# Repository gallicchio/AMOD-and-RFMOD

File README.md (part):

# AMOD and RF-MOD: boards of analog and RF building blocks

Nine 100 x 100 mm boards of "tiles" for an FPGA with fast converters: seven first-level boards (for the ECP5-2ADC-2DAC
board, or an Icepi Zero with its AD9280/AD9708 module), among them AMOD-N, as simple as the first, the conversion board
AMOD-C and two motor boards, AMOD-M (brushed motors and actuators) and AMOD-B (a brushless gimbal motor), and two
second-level boards built around the ECP5-2ADC-2DAC board's two DACs and two ADCs: PhMOD (AMOD-2 until Prompt 17) and
IQ-MOD.  Each tile is one circuit with its own SMA jacks: cable a DAC to its input and its
output to an ADC, and compare the measurement with the expected result printed beside it.  The silkscreen draws every
tile's wiring as it is laid in copper.  The tutorial they serve is `icepi-zero-dac-adc/tutorial/`, whose Appendix D
specified them.

Rev A, 2026-10-25 (AMOD-N, AMOD-C, AMOD-M and AMOD-B added 2026-10-28).  Designed by Claude with Jason Gallicchio.  Ordered
from JLCPCB from 2026-10-29; some of the boards have come in, all untested as of 2026-11-16 (which ones, and how many are
assembled, goes into `BRINGUP.md` when Jason says).  The bring-up is [`BRINGUP.md`](BRINGUP.md); what rev B changes is
[`bringup/REVB.md`](bringup/REVB.md), which since 2026-11-16 includes a pin audit's findings on the built boards.

**The rev A Pmod plugs are not standard** (Jason, 2026-11-16).  They were drawn to mate with ECP5-2ADC-2DAC rev A's
sockets, and both are mirrored end to end against the Pmod specification: a rev A board belongs only in an ECP5-2ADC-2DAC
rev A, never in a standard Pmod host, module or cable, where its 3.3 V and ground meet I/O lines.  The rev A boards are
marked so.  Rev B's plugs will follow the specification, as the redrawn Icepi adapter's socket now does.

| board | what | tiles | layers | parts per board |
|---|---|---|---|---|
| [AMOD-P](docs/HANDBOOK_amod_p.md) | passive: pads, RC and LC filters, resonators, a crystal, a clipper, a delay line, LEDs, an AM loopstick | 13 | 2 | $17.07 |
| [AMOD-N](docs/HANDBOOK_amod_n.md) | the second passive board: calibration standards, two splitters, a quarter-wave stub, a low-pass, a diode detector, a bias-T, a 1:1 balun and a 1:4 transformer; a step attenuator (by hand or the FPGA) and an oscillator on the Pmod's 3.3 V | 11 | 4 | $43.91 |
| [AMOD-A](docs/HANDBOOK_amod_a.md) | active on USB-C: gain blocks, an HF LNA, an HB100 Doppler radar, a one-pin ADC, a 4046 PLL, heat, a mixer, impedance and I-V, ultrasound, audio | 12 | 4 | $49.73 |
| [AMOD-C](docs/HANDBOOK_amod_c.md) | conversion: two regulators and an electronic load, a charge pump, switched capacitors (a filter, a resistor), a delta-sigma modulator, a track-and-hold, a SAR comparator, a differential pair, a cascode, a V-to-F, a precision rectifier | 12 | 4 | $43.93 |
| [AMOD-M](docs/HANDBOOK_amod_m.md) | motors on a 5-16 V supply: a DC motor with its encoder, a stepper, a servo, a solenoid's flyback three ways, a DC-coupled bridge amplifier, a buck power stage, and a hall, an optical and a load-cell sensor for their loops | 11 | 4 | $36.49 |
| [AMOD-B](docs/HANDBOOK_amod_b.md) | a brushless gimbal motor on a 5-12 V supply: a three-phase driver from the FPGA, the motor over a magnetic encoder, two halls and an index sensor, its back-EMF, its phase and bus currents, its vibration, and an IMU | 12 | 4 | $42.45 |
| [RF-MOD](docs/HANDBOOK_rf_mod.md) | 915 MHz and 2.4 GHz: a diode-ring mixer, two filters, a QPL9547 LNA, a gain block, two ADL5350 mixers, a synthesizer with two outputs, a TRF3722 I/Q transmitter, power and a 25 MHz reference | 10 | 4 | $66.51 |
| [PhMOD](docs/HANDBOOK_phmod.md) | physics at HF, magnetic resonance, the ionosphere and light: a 1 W pulse amplifier and duplexer, a two-channel HF receiver, a VLF loop amplifier, a reflection bridge, coupled resonators, a coil driver, a noise source, a laser driver with an RF bias-T | 10 | 4 | $77.89 |
| [IQ-MOD](docs/HANDBOOK_iq_mod.md) | coherent I/Q and microwave physics, 0.4-6 GHz: an I/Q modulator and demodulator on one synthesizer's two outputs, a dual directional coupler, an LNA, a log detector, a switch, a noise source, GNSS, an ODMR loop | 11 | 4 | $99.71 |
| [Icepi adapter](icepi_adapter/README.md) | the tutorial's 2x12 Icepi Zero adapter with a Pmod socket, redrawn to the Pmod standard on 2026-11-16 (never built; a rev A AMOD plug fits it only upside down) | | 4 | hand-soldered |

Each tile's name and what it does are printed on the board: the jacks' names sit on their own tile's frame beside each
jack, a tile's title in words on its top frame where it fits, its ranges and levels inside it.  Ports are named in
capitals (IN, OUT, LO), tiles in mixed case (Step attenuator, Diode mixer), everything else in lower case.  Turn a board
over and each tile has a panel on the back under it: its limits, its loads, its supply, and where there is room a small
plot of the response to expect, so the board can be cabled without the handbook open.  Below, each board's
picture and a table of its tiles, each row a summary of the tile's entry in the board's handbook (linked from the tile's
number), where the tile has its own picture, what to expect, the circuit and its parts.  What to buy beside the boards,
with links and prices, is in [docs/KIT.md](docs/KIT.md).

## The boards

<!-- board:amod_p -->
### [AMOD-P](docs/HANDBOOK_amod_p.md): the passive board

| tile | what it does | chip | specs | limits | experiments | how to use it | you need |
|---|---|---|---|---|---|---|---|
| [**p1**](docs/HANDBOOK_amod_p.md#p1) pi pad | Divides the voltage by 10 (-20 dB) and looks like 50 ohm from both ports. | passive | 61.9 / 249 / 61.9 ohm pi; -20.0 dB; DC to well past 30 MHz. | -20 dB only between 50 ohm on both sides (-14 dB into a high impedance); about 0.1 W (+-3 V) at IN. | A known weak signal for a receiver or LNA; padding a mismatched cable; checking the ADC's 50 ohm setting. | DAC to IN, OUT to the ADC set to 50 ohm. | Nothing beyond SMA cables. |
| [**p2**](docs/HANDBOOK_amod_p.md#p2) RC low-pass | A first-order RC low-pass: passes below 159 kHz and falls 20 dB per decade above. | passive | 1 k and 1 nF; -3 dB at 159 kHz; time constant 1 us. | OUT is a 1 k source: read it on the ADC's high-impedance setting (50 ohm divides it by 21). | A Bode plot, 45 degrees at the corner, the step response, the lag plant for feedback control. | DAC to IN, OUT to the ADC on high impedance; sweep the frequency or send a step. | Nothing beyond SMA cables. |
| [**p3**](docs/HANDBOOK_amod_p.md#p3) RC high-pass | A first-order RC high-pass, the mirror image of p2. | passive | 1 nF and 1 k; -3 dB at 159 kHz; +20 dB per decade below. | OUT is a 1 k source: read it on high impedance. | A Bode plot, AC coupling, a differentiator (a step gives a 1 us spike). | DAC to IN, OUT to the ADC on high impedance. | Nothing beyond SMA cables. |
| [**p4**](docs/HANDBOOK_amod_p.md#p4) series RLC | A series 100 uH and 220 pF resonator between 50 ohm ports: a band-pass peak that the DIP switch moves. | passive | 1.07 MHz with both switches off, 0.98 (way 1, +47 pF), 0.89 (way 2, +100 pF), 0.83 (both); Q about 6. | The 50 ohm ports load it: Q is 6, where the coil alone would allow about 60. | Resonance and Q, the phase through resonance, tracking a resonance with a lock-in or a PLL, a resonant plant to control. | Sweep the DAC into IN, OUT to the ADC (50 ohm); set the DIP switch. | Nothing beyond SMA cables. |
| [**p5**](docs/HANDBOOK_amod_p.md#p5) LC low-pass | A 5th-order Butterworth LC low-pass at 9 MHz: the anti-alias filter for a 25 MS/s ADC, or the smoothing filter after a DAC. | passive | -3 dB at 8.9 MHz, -30 dB at 18 MHz; 50 ohm in and out. | The response is as designed only with 50 ohm on both ports. | Aliasing with and without it; a filter's magnitude, phase and group delay; cleaning a DAC's staircase. | Between the DAC and its load, or between a signal and the ADC (50 ohm). | Nothing beyond SMA cables. |
| [**p6**](docs/HANDBOOK_amod_p.md#p6) LC low-pass | A 3rd-order LC low-pass near 120 kHz: turns a one-bit (delta-sigma or PWM) stream into a tone. | passive | 10 nF, 150 uH, 10 nF (C0G); -3 dB at 118 kHz; 50 ohm. | Designed for 50 ohm on both ports. | One-bit DAC reconstruction, delta-sigma noise shaping seen at the output, a slow plant for control. | DAC (or a one-bit stream through 50 ohm) to IN, OUT to the ADC. | Nothing beyond SMA cables. |
| [**p7**](docs/HANDBOOK_amod_p.md#p7) band-pass | A 3rd-order LC band-pass, 4.7-7.5 MHz: the band round the tutorial's 6.25 MHz digital-communications carrier. | passive | Peak at 6.3 MHz, -3 dB from 4.7 to 7.5 MHz; 50 ohm. | Only 3rd order: the skirts fall about 18 dB per octave. | Band-limiting a modem's chips (spread spectrum, LoRa chirps); a transmitter's harmonics removed; a receiver's front end. | In line between the DAC and the ADC, or ahead of a receiver. | Nothing beyond SMA cables. |
| [**p8**](docs/HANDBOOK_amod_p.md#p8) quartz crystal | A 4 MHz quartz crystal in series between the jacks: a very sharp pass at its series resonance and a notch at its parallel resonance about 6 kHz above. | passive | f_s near 4.000 MHz (-3.7 dB); f_p about 6 kHz higher; Q about 50,000 (C_m 15 fF, C_0 4 pF). | Needs frequency steps of a few hertz (the FPGA's NCO); keep the drive under about +-1 V (crystals have a drive-level limit near 100 uW). | Q from the width and from the ring-down; series against parallel resonance; pulling f_p with a capacitor across OUT (an SMA tee); the temperature coefficient. | Sweep the DAC slowly through 4.000 MHz into IN, OUT to the ADC, lock-in detection in the gateware. | An SMA tee and a few capacitors (or open cable stubs) for the pulling experiment. |
| [**p9**](docs/HANDBOOK_amod_p.md#p9) ceramic res. | A 455 kHz ceramic resonator in series: a pass at 455 kHz and a notch a few kHz above; the AM superhet's IF element. | passive | Q of a few hundred: between p4's LC (6) and p8's quartz (50,000). | A two-terminal resonator, not a three-terminal IF filter: one peak, no flat passband. | Q compared across LC, ceramic and quartz; an IF stage for a superhet built in gateware. | Sweep 440-480 kHz into IN, OUT to the ADC. | Nothing beyond SMA cables. |
| [**p10**](docs/HANDBOOK_amod_p.md#p10) clipper | 1 k in series and a 1N4148 diode each way to ground: clips any signal to about +-0.6 V. | passive | Clips at +-0.6 V; a 1 k source. | Read OUT on high impedance; up to +-4 V in (the 1 k holds the diode current to 4 mA). | Harmonics of a clipped sine against amplitude; odd harmonics, and even ones with a DC offset added; distortion. | DAC sine to IN, OUT to the ADC on high impedance, FFT in the gateware or Python. | Nothing beyond SMA cables. |
| [**p11**](docs/HANDBOOK_amod_p.md#p11) delay line | A 400 ns, 50 ohm delay line made of 20 LC sections, with taps every 100 ns: 260 feet of RG-58 on a board. | passive | Z0 51 ohm, 20 ns a section, cut-off 16 MHz, flat to about 10 MHz; taps through 470 ohm. | Disperses near 16 MHz (a chirp spreads); a tap is x1 into a high impedance, /10 into 50 ohm. | Reflections from an open, a short and a matched end; time-domain reflectometry; echoes for an equalizer; a radar target on a cable; a pure-delay plant for control. | A pulse or chirp from the DAC into IN; OUT open, shorted or terminated; the taps and OUT to the ADCs. | An SMA short and a 50 ohm terminator (the kit's ANNE-50+) for the reflection experiments. |
| [**p12**](docs/HANDBOOK_amod_p.md#p12) LEDs | Four LEDs (red, yellow, green, blue) behind 100 ohm, one at a time from the DIP switch: Planck's constant from the voltage where each starts to glow. | passive | 630, 596, 525 and 469 nm (DIP ways 1-4); 100 ohm in series; IN 0-5 V. | The InGaN green and blue sit above the line (their knee is not just hc / e lambda); the colours are not printed, so light them. | Planck's constant; LED I-V curves (with AMOD-A's a10); light against current. | Ramp the DAC (or the host's LED output) into IN and read the LED loop's voltage; one DIP way at a time. | Nothing (a dark room helps). |
| [**p13**](docs/HANDBOOK_amod_p.md#p13) AM loopstick | An AM-band antenna: a ferrite-rod coil screwed into the terminal, tuned by four switched capacitors or an external tuning capacitor on VAR C, its tap on the jack. | passive | With a 330 uH coil: 1.28 MHz (47 pF) down to 0.40 MHz (470 pF), and the sums between; the kit's 240 uH coil tunes about 17 % higher. | The switches tune in 15 steps; continuous tuning needs a capacitor on VAR C (a polyvaricon and its dial are 20 mm square: no room on the tile).  A weak signal that needs a4's gain before the ADC. | Real AM stations; the resonance and Q of a loopstick; the tutorial's AM radio gateware. | Coil ends to GND and HOT, its tap (if it has one) to TAP; rod along the bottom edge with two cable ties; OUT to AMOD-A's a4, a4 to the ADC; the DIP picks the band, or a tuning capacitor on VAR C (frame to GND) tunes within it. | An AM loopstick coil and two cable ties (kit: Atomic-29 240 uH loopstick, Panduit PLT1M-C); optionally a 365 pF tuning capacitor with a knob (kit: Amplified Parts single-section 365 pF). |

More on each tile, with its picture, in the [AMOD-P handbook](docs/HANDBOOK_amod_p.md); what to buy in [KIT.md](docs/KIT.md).

<!-- /board:amod_p -->

<!-- board:amod_n -->
### [AMOD-N](docs/HANDBOOK_amod_n.md): the second passive board

| tile | what it does | chip | specs | limits | experiments | how to use it | you need |
|---|---|---|---|---|---|---|---|
| [**n1**](docs/HANDBOOK_amod_n.md#n1) calibration | Calibration standards for a network analyzer, on the board: a short and an open at the jacks' pins, a 50 ohm load, a 25 ohm check standard and a thru. | passive | SHORT: the centre pin poured to ground all round.  OPEN: the bare pin.  LOAD: 2 x 100 ohm at the end of 4 mm of 50 ohm line.  25 OHM: 2 x 49.9 ohm (VSWR 2, \|Gamma\| 1/3, 9.5 dB return loss).  THRU: 19.8 mm of 50 ohm coplanar line, about 115 ps. | The standards are modelled, not measured: the open's fringing (tens of fF) and the short's inductance (tens of pH) count above about 3 GHz, and the 0402 load is a 20 dB return loss at 3 GHz.  Check them once against the NanoVNA's SMA standards. | A full SOLT calibration of IQ-MOD's reflectometer (q1, q2, q5) or of a NanoVNA at the board's surface; the 25 ohm standard as its check; every other tile then measured from its pads with its jacks taken out (they are all the same part). | The analyzer's port to SHORT, OPEN and LOAD in turn; its two ports to THRU A and THRU B for the two-port step; then any tile. | Nothing beyond SMA cables. |
| [**n2**](docs/HANDBOOK_amod_n.md#n2) resistive splitter | A resistive power splitter: three 16.9 ohm in a star, every port 50 ohm, 6 dB from any port to either other, from DC to 6 GHz. | passive | 3 x 16.9 ohm (50 / 3); -6.0 dB each way; DC-6 GHz; OUT 1 and OUT 2 on lines of equal length. | No isolation (OUT 1 to OUT 2 is also -6 dB); 6 dB of loss where a transformer splitter loses 3; about +20 dBm at IN (1/16 W resistors). | One DAC into both ADCs to measure the converters' own gain and skew; the reference and test paths of a scalar network analyzer; its isolation against n3's. | IN from the source; OUT 1 and OUT 2 to two 50 ohm loads.  Symmetric: any port can be IN. | Nothing beyond SMA cables. |
| [**n3**](docs/HANDBOOK_amod_n.md#n3) transformer splitter | A transformer power splitter (and combiner): half the power to each port, 3 dB, with the two ports isolated from each other, 0.5-400 MHz. | [ADP-2-1+](https://www.minicircuits.com/WebStore/dashboard.html?model=ADP-2-1%2B) | 3.1-3.4 dB from SUM to each port; 25-34 dB between port 1 and port 2; 0.5-400 MHz (the datasheet). | A transformer: nothing below 0.5 MHz; the isolation holds only with 50 ohm on all three ports; pins 2 and 5 are joined and must not be grounded. | Two DACs combined into one amplifier for a two-tone intermodulation test (AMOD-A's a4, PhMOD's h5); one reference split to two boards; isolation measured against n2's. | SUM from the source (or to the load when combining); PORT 1 and PORT 2 to two loads (or from two sources). | Nothing beyond SMA cables. |
| [**n4**](docs/HANDBOOK_amod_n.md#n4) quarter-wave stub | A quarter-wave open stub hanging off a 50 ohm line: at 2.45 GHz it is a short circuit at the junction, so the line has a notch there. | passive | 17.3 mm of 50 ohm coplanar waveguide, open at its end; a notch near 2.45 GHz and 7.35 GHz; the line passes at DC and 4.9 GHz. | The notch sits where the line's effective permittivity puts it (3.1 was assumed): within a few percent of 2.45 GHz.  Its depth is set by the line's loss. | Sweep it with RF-MOD's synthesizer into IQ-MOD's log detector, or with a VNA; read the line's effective permittivity from the notch; a Wi-Fi notch ahead of a receiver; the tutorial's coaxial quarter-wave stub at microwave frequencies. | IN from a source, OUT to a detector or a VNA's second port. | Nothing beyond SMA cables. |
| [**n5**](docs/HANDBOOK_amod_n.md#n5) low-pass | A low-pass filter: passes DC to 1 GHz, stops 1.9-5 GHz, so a 915 MHz synthesizer's harmonics are gone. | [LFCN-1000+](https://www.minicircuits.com/WebStore/dashboard.html?model=LFCN-1000%2B) | 0.3 dB at 500 MHz, 0.8 dB at 1 GHz, 3 dB at 1.3 GHz, 26 dB at 1.5 GHz, 30 dB from 1.9 to 5 GHz (the datasheet). | 50 ohm on both sides; the stopband rises again above about 5 GHz (20 dB at 5.5 GHz). | A MAX2871's square-ish 915 MHz made a sine (its harmonics before and after on a spectrum analyzer); an image filter ahead of a receiver below 1 GHz. | IN from the source, OUT to the load. | Nothing beyond SMA cables. |
| [**n6**](docs/HANDBOOK_amod_n.md#n6) detector | A diode detector: RF power in, DC out.  Two zero-bias Schottky diodes as a voltage doubler, square-law at low power and linear at high. | [SMS7630](https://www.skyworksinc.com/Products/Diodes/SMS7630-Series) | 51 ohm across IN; 10 nF in; a SMS7630 pair as a doubler; 100 pF and 100 k on OUT (about 1 us); 10 MHz-6 GHz; square law below about -20 dBm. | OUT must go to a high impedance (the ADC's high-Z setting): 50 ohm shorts it.  Microvolts at the bottom (the x100 input below -40 dBm); temperature moves its zero; +10 dBm at most (the diodes' 1 V breakdown). | Square law against the AD8318's log law (IQ-MOD); an AM envelope detector after AMOD-P's loopstick and AMOD-A's LNA; a radiometer's power detector; the shape of PhMOD's transmit pulses. | IN from the RF; OUT to an ADC on its high-impedance setting. | Nothing beyond SMA cables. |
| [**n7**](docs/HANDBOOK_amod_n.md#n7) bias-T | A bias-T: puts DC from a bench supply onto an RF line and keeps it off the RF side. | passive | 100 nF in series; 27 nH + 330 nH + 10 uH from the DC loop to RF+DC; 100 nF across the DC; about 2 MHz-3 GHz; up to 100 mA and 16 V. | Below about 2 MHz the 10 uH stops blocking; 100 mA (the 330 nH) and 16 V (the capacitors); never put RF+DC into a jack that cannot take the DC. | An active GPS antenna or an LNA at the end of a cable powered through the coax; a varactor or a detector diode biased through its own signal line; the bias-T's own leakage of RF into the supply. | RF to the instrument, RF+DC to the device, the bench supply's clips on the DC and GND loops. | A bench supply with clip leads. |
| [**n8**](docs/HANDBOOK_amod_n.md#n8) step attenuator | A digital step attenuator: 0 to 31.75 dB in 0.25 dB steps from 9 kHz to 6 GHz, set by hand on an 8-way switch or by the FPGA over three Pmod lines. | [PE43711](https://www.lcsc.com/product-detail/C470929.html) | 7 bits, 0-31.75 dB in 0.25 dB; 1.5-2.8 dB of loss at 0 dB.  By hand: switch way 1 (SPI) off, ways 2-8 the bits 0.25, 0.5, 1, 2, 4, 8 and 16 dB (on = that much more), the chip's direct parallel mode.  By the FPGA: ways 2-8 off, way 1 on; SDATA on IO2, SCLK on IO3, LE on IO4, 8 bits (bit 7 = 0, then 4 x dB), least significant first.  3.3 V and 150 uA from the Pmod either way. | +23 dBm above 48 MHz, less below (about +9.5 dBm under 0.5 MHz, +15 dBm at 5 MHz); a few tenths of a dB of step error; dark unless the board is plugged into the host's Pmod (rev A boards: ECP5-2ADC-2DAC rev A only, its sockets are non-standard as this plug is) (the chip is an active switch array, even when set by hand); in SPI mode every bit switch must be off. | The 1 dB compression point and IP3 of every amplifier and mixer on the boards; noise figure by the Y-factor; bit-error rate against signal-to-noise for the tutorial's modems; the log detector's slope; an automatic gain control loop in gateware. | Plug AMOD-N into the host's Pmod (rev A boards: ECP5-2ADC-2DAC rev A only, its sockets are non-standard as this plug is); IN from the source, OUT to the device.  Set the level on the switch with way 1 off, or turn the bits off and way 1 on and write the word from the FPGA (RF-MOD's SPI peripheral with its own LE). | Nothing beyond SMA cables. |
| [**n9**](docs/HANDBOOK_amod_n.md#n9) oscillator | An oscillator made of one transistor and a tank, tunable by a voltage and lockable to an outside tone. | [MMBT3904](https://www.lcsc.com/product-detail/C20526.html), [BB133](https://www.lcsc.com/product-detail/C5334579.html) | A Clapp (series-tuned Colpitts) on an MMBT3904 at about 1.5 mA; 10 uH and a BB133 varactor; 9.6-11.5 MHz for TUNE from -2 to +2 V (10.5 MHz at 0 V); about -22 dBm into 50 ohm; the Pmod's 3.3 V, switched. | Free-running LC: it drifts with temperature; the frequencies are calculated to within about 10 %; the output is small (22 pF from the emitter) so the load does not pull it. | Injection locking: a DAC tone near its frequency on TUNE pulls it in over a range that grows with the tone's amplitude (Adler's equation); FM from a DAC; its phase noise against the MAX2871's and a crystal's; a phase-locked loop closed in the FPGA (phase from an ADC, control on TUNE). | Plug the board into the host's Pmod (rev A boards: ECP5-2ADC-2DAC rev A only, its sockets are non-standard as this plug is) and slide the switch up; OUT to an ADC (the x10 input); TUNE from a DAC. | Nothing beyond SMA cables. |
| [**n10**](docs/HANDBOOK_amod_n.md#n10) 1:1 transformer | A 1:1 transformer whose OUT jack floats: a balun for a dipole, and a break in a ground loop. | [TC1-1TG2+](https://www.minicircuits.com/WebStore/dashboard.html?model=TC1-1TG2%2B) | 0.4-500 MHz; 0.3 dB of loss at 10 MHz, 0.5 dB at 100 MHz, 1.8 dB at 500 MHz (the datasheet); OUT's four legs on an island with no ground within 5.6 mm on any layer. | 0.25 W and 30 mA DC (the datasheet); nothing below 0.4 MHz; the island's few pF to the board limit the common-mode isolation as the frequency rises. | The tutorial's HF dipole fed balanced (OUT's pin and shell to its two halves); a ground loop between the host and a mains-powered instrument broken (watch the hum go); a floating measurement. | IN from the source; OUT through an SMA-to-clips lead to the dipole or the floating load. | An SMA-to-two-clips lead (KIT.md) for a dipole. |
| [**n11**](docs/HANDBOOK_amod_n.md#n11) 1:4 transformer | A 1:4 transformer: OUT's impedance is four times IN's and its voltage twice; a DIP switch puts a known load on OUT. | [TC4-1W+](https://www.minicircuits.com/WebStore/dashboard.html?model=TC4-1W%2B) | 3-800 MHz; 0.8 dB mid-band, 1.1 dB at 3 MHz, 2.2 dB at 800 MHz (the datasheet); switch 1: 200 ohm across OUT (IN reads 50); switch 2: 49.9 ohm (IN reads 12.5). | Nothing below 3 MHz; OUT is referenced to ground (the secondary's low end is grounded), so it is a step-up transformer here, not a balun. | The turns ratio squared measured: IN's impedance with each load (PhMOD's h7 or a VNA); a 200 ohm source or load matched to 50 ohm; twice the voltage at OUT. | IN from the source or the analyzer; OUT open, to a load, or loaded by the switch. | Nothing beyond SMA cables. |

More on each tile, with its picture, in the [AMOD-N handbook](docs/HANDBOOK_amod_n.md); what to buy in [KIT.md](docs/KIT.md).

<!-- /board:amod_n -->

<!-- board:amod_a -->
### [AMOD-A](docs/HANDBOOK_amod_a.md): the active board

| tile | what it does | chip | specs | limits | experiments | how to use it | you need |
|---|---|---|---|---|---|---|---|
| [**a1**](docs/HANDBOOK_amod_a.md#a1) power | Power: 5 V from USB-C, and -5 V and 3.3 V made from it; a socket carries the rails to a breadboard. | [LM2664](https://www.ti.com/product/LM2664), [TPS7A20](https://www.ti.com/product/TPS7A20) | +5 V up to 1.5 A, -5 V at 40 mA, +3.3 V at 300 mA; green LED 5 V, red LED -5 V. | -5 V is 40 mA: about four op-amp tiles at once.  The board negotiates nothing: use a plain 5 V supply. | - | Plug in the USB-C; then switch on each tile you use (slider up). | A 5 V USB-C supply, 1.5 A or more (kit: Raspberry Pi 5.1 V 3 A supply). |
| [**a2**](docs/HANDBOOK_amod_a.md#a2) x10 | An op-amp gain block: x10 (20 dB) to 14 MHz, with a 50 ohm input. | [OPA810](https://www.ti.com/product/OPA810) | x10 into a high impedance (x5 into 50 ohm); -3 dB at 14 MHz; IN up to +-0.4 V for +-4 V out. | 140 MHz gain-bandwidth sets the bandwidth; clips at +-4 V. | The gain-bandwidth trade (compare a3); slew rate and clipping; amplifying a photodiode, a noise source or a weak tone. | Signal to IN, OUT to the ADC (high impedance for the full x10). | Nothing beyond SMA cables. |
| [**a3**](docs/HANDBOOK_amod_a.md#a3) x100 | The same op-amp stage at x100 (40 dB), to 1.4 MHz. | [OPA810](https://www.ti.com/product/OPA810) | x100; -3 dB at 1.4 MHz; IN up to +-40 mV. | Only 1.4 MHz wide (gain-bandwidth); for 40 dB at HF use a4. | Gain-bandwidth against a2 and a4; small audio and ultrasonic signals. | Signal to IN, OUT to the ADC. | Nothing beyond SMA cables. |
| [**a4**](docs/HANDBOOK_amod_a.md#a4) LNA | An HF low-noise amplifier: x100 (40 dB) flat from 1 to 30 MHz, about 3 dB noise figure from 50 ohm. | [OPA847](https://www.ti.com/product/OPA847) | x101; flat 1-30 MHz (-3 dB near 39 MHz); 0.85 nV/rtHz. | IN under +-30 mV; the OPA847 is stable only at gains above 12 (do not lower the gain). | AM and shortwave reception with a wire antenna or p13's loopstick; noise figure; weak-signal work. | Antenna (or p13's OUT) to IN, OUT to the ADC. | An antenna for over-the-air use: a few metres of wire on an SMA, or AMOD-P's p13. |
| [**a5**](docs/HANDBOOK_amod_a.md#a5) Doppler | A socket and amplifier for an HB100 10.525 GHz Doppler radar module: the beat between what it sends and what comes back, x101. | [HB100 (module)](https://www.amazon.com/dp/B07YY6FD4T), [OPA810](https://www.ti.com/product/OPA810) | 70 Hz per m/s of speed toward or away (19.4 Hz per km/h); x101 to OUT. | The HB100 has one mixer, not I and Q: it measures speed but not direction, and gives no range (it is a CW radar). | The speed of a hand, a pendulum, a fan's blades, breathing; Doppler spectra (micro-Doppler). | Wire the module's +5 V, IF and GND pins to the +5 / IF / G header with jumper wires (the pin order differs between modules: follow its print); OUT to an ADC (the host's x10 input helps); point it at something moving. | An HB100 module and three female-female jumper wires (kit: MH-ET Live HB100 X, about $14). |
| [**a6**](docs/HANDBOOK_amod_a.md#a6) 1-bit ADC | A one-bit (delta-sigma) ADC made of a comparator and an RC integrator, with the FPGA as the flip-flop: an ADC from one Pmod input and one Pmod output. | [TLV3501](https://www.ti.com/product/TLV3501) | IN 0-3.3 V (or +-1.5 V AC-coupled), 10 k input; integrator 10 k / 10 nF; clock the loop at 1-10 MHz. | First order: about 9 dB more resolution per doubling of the oversampling ratio; works only with its gateware. | Delta-sigma conversion, oversampling and noise shaping, decimation (CIC) filters, trading speed for bits. | The gateware reads the comparator on Pmod IO7 every clock, registers it, and drives the registered bit back out on IO8; low-pass and decimate that bit stream.  Signal to IN. | Nothing (the gateware). |
| [**a7**](docs/HANDBOOK_amod_a.md#a7) PLL 4046 | A 74HC4046 phase-locked loop: its VCO locks to a 50-200 kHz signal on IN. | [74HC4046A](https://www.lcsc.com/product-detail/C546981.html) | VCO near 100 kHz (10 k, 1 nF); phase comparator 2 with a 10 k / 100 nF lag filter; VCO OUT 5 V CMOS through 470 ohm. | Fixed loop filter and VCO range (no switches); locks at x1 (no divider); no test loops: probe pins 9 and 13. | Lock and capture range; FM demodulation (pin 9 is the VCO's control voltage); loop dynamics and ringing; an analog PLL against the FPGA's. | DAC sine or square (more than 0.4 V peak) to IN, VCO OUT to an ADC; sweep or frequency-modulate the DAC. | A scope probe for pins 9 and 13. |
| [**a8**](docs/HANDBOOK_amod_a.md#a8) heat | A 0.83 W heater (two 15 ohm resistors) switched from a Pmod line, with a temperature sensor beside it: a thermal plant to control. | [TMP235](https://www.ti.com/product/TMP235) | 30 ohm, 170 mA, 0.83 W while Pmod IO6 is high; TEMP OUT 10 mV/K + 500 mV (750 mV at 25 C). | On or off from IO6 (PWM it for proportional power); it heats a few square centimetres, with a time constant of tens of seconds.  The heater has no jack: DRIVE IN beside it belongs to a10. | A thermal time constant; bang-bang against PID control; warming a part taped to the heater. | PWM from the FPGA on Pmod IO6; TEMP OUT to an ADC. | Nothing (Kapton tape to hold a part on the heater, if you like). |
| [**a9**](docs/HANDBOOK_amod_a.md#a9) mixer | A Gilbert-cell double-balanced mixer (MC1496): IF OUT is RF times LO, the sum and difference frequencies. | [MC1496](https://www.lcsc.com/product-detail/C7295.html) | RF and LO +-0.3 V into 51 ohm; 1 k emitter degeneration, 1 mA a side; IF OUT single-ended from a 1.5 k load; about 0.3 V of IF per volt of RF at 0.3 V of LO. | IF OUT is a 1.5 k source: a metre of coax (100 pF) rolls it off near 1 MHz, so keep the IF low or the cable short and use high impedance.  LO feedthrough about -40 dB (no null trimmer).  RF and LO are good to a few tens of MHz. | Mixing and images; AM demodulation as a product detector; the AM radio; PSK demodulation with a recovered carrier. | RF and LO from the two DACs (or an antenna through a4 on RF); IF OUT to an ADC on high impedance. | Nothing beyond SMA cables. |
| [**a10**](docs/HANDBOOK_amod_a.md#a10) impedance | Measures a part's impedance and I-V curve: drives it through a known resistor and reads the voltage on both sides. | [OPA810](https://www.ti.com/product/OPA810) | DRIVE IN x2 is node S; the DIP picks R = 47, 470, 4.7 k or 47 k from S to X; the part goes from X (the DUT jack) to ground; S OUT and X OUT give half of each node into 50 ohm; Z = R X / (S - X); +-4 V, up to 40 mA. | DC to a few MHz; most accurate when Z is near the chosen R; calibrate with the DUT open and shorted. | Impedance spectra of resistors, capacitors, inductors, a crystal and a speaker; LED and diode I-V curves (Planck with p12's colours); a low-frequency Smith chart. | DAC to DRIVE IN; S OUT to ADC 1 and X OUT to ADC 2; the part on the DUT jack; one DIP way on (the reference R); the gateware takes the complex ratio at each frequency. | A way to put a part on the DUT jack: an SMA-to-minigrabber lead or a part soldered to an SMA plug. |
| [**a11**](docs/HANDBOOK_amod_a.md#a11) ultrasound | 40 kHz ultrasound: an H-bridge drives the transmitter from two Pmod lines, and the receiver's signal comes out x100. | [DRV8837](https://www.ti.com/product/DRV8837), [OPA810](https://www.ti.com/product/OPA810) | TX gets 10 V p-p from Pmod IO4 / IO3 in antiphase; RX x100 behind a 4 kHz high-pass; 5.8 us per mm there and back.  The slide switch's 5 V powers the two amplifiers: the TX H-bridge (each end of the transducer swings 0-5 V, in antiphase) and the RX op amp's positive rail (its negative rail is the board's -5 V). | Only at the transducers' 40 kHz resonance; the receiver hears the transmitter directly for the first few hundred microseconds. | The speed of sound, echo ranging (sonar), Doppler, beam patterns, an ultrasonic data link. | Transmitter in the TX socket, receiver in the RX socket (pins 1 and 5 of each); the gateware sends 8-20 cycles of 40 kHz on IO4 and IO3 in antiphase; RX OUT to an ADC; hold a reflector above the board. | A pair of 40 kHz transducers (kit: PUI UT-1640K-TT-2-R and UR-1640K-TT-2-R). |
| [**a12**](docs/HANDBOOK_amod_a.md#a12) audio | Audio: a 2.5 W class-D amplifier into a speaker, fed from a DAC or a one-bit Pmod stream, and an electret microphone amplified x100. | [PAM8302A](https://www.diodes.com/assets/Datasheets/PAM8302A.pdf), [OPA810](https://www.ti.com/product/OPA810) | Up to 2.5 W into 4 ohm (about 1.5 W into 8); SPEAKER IN +-1 V; the one-bit stream on Pmod IO2 through 10 k / 10 nF; MIC OUT x100. | Mono; the class-D output is unfiltered (the speaker is the filter); the microphone hears the speaker. | An acoustic modem (FSK, MSK through the air); the speed of sound in air; a room's echoes and impulse response; one-bit (PDM) audio. | Speaker wires in the SPK terminal, the electret in the MIC socket (+ to pin 1); DAC to SPEAKER IN or a one-bit stream on IO2; MIC OUT to an ADC. | A small speaker and an electret capsule (kit: Adafruit 6486 36 mm 8 ohm speaker, SparkFun COM-08635 electret). |

More on each tile, with its picture, in the [AMOD-A handbook](docs/HANDBOOK_amod_a.md); what to buy in [KIT.md](docs/KIT.md).

<!-- /board:amod_a -->

<!-- board:amod_c -->
### [AMOD-C](docs/HANDBOOK_amod_c.md): the conversion board

| tile | what it does | chip | specs | limits | experiments | how to use it | you need |
|---|---|---|---|---|---|---|---|
| [**c1**](docs/HANDBOOK_amod_c.md#c1) power | Power: 5 V from USB-C, and -5 V and 3.3 V made from it; a socket carries the rails to a breadboard (AMOD-A's a1). | [LM2664](https://www.ti.com/product/LM2664), [TPS7A20](https://www.ti.com/product/TPS7A20) | +5 V up to 1.5 A, -5 V at 40 mA, +3.3 V at 300 mA; green LED 5 V, red LED -5 V. | -5 V is 40 mA: the five tiles on +-5 V draw about 25 mA together.  The board negotiates nothing: use a plain 5 V supply. | - | Plug in the USB-C and the host's Pmod (rev A boards: ECP5-2ADC-2DAC rev A only, its sockets are non-standard as this plug is); then switch on each tile you use (slider up). | A 5 V USB-C supply, 1.5 A or more (kit: Raspberry Pi 5.1 V 3 A supply). |
| [**c2**](docs/HANDBOOK_amod_c.md#c2) regulators | A buck converter, an LDO after it and an electronic load: the ripple before and after the LDO, load steps, dropout. | [TLV62568](https://www.ti.com/product/TLV62568), [TPS7A20](https://www.ti.com/product/TPS7A20), [OPA810](https://www.ti.com/product/OPA810), [AO3400A](https://www.lcsc.com/product-detail/C20917.html) | Buck: 3.6 V at 1.5 MHz from the switched 5 V, 2.2 uH, 10 uF in and out; TRIM through 100 k into its feedback node: OUT = 4.2 V - TRIM (open: 3.6 V).  LDO: 3.3 V, about 40 dB of rejection at 1.5 MHz.  Load: 100 mA per volt on LOAD (terminated in 49.9 ohm), from the LDO's output through an AO3400A and 10 ohm.  BUCK~ and LDO~ are the two outputs AC-coupled through 1 uF and 49.9 ohm. | LOAD 0 to 1 V (100 mA: the 10 ohm 0805 then dissipates 0.1 W, the FET 0.23 W).  Below about 3.5 V on its input (TRIM above +0.7 V) the LDO drops out.  The buck skips pulses below about 150 mA, so its ripple changes character with load. | Output ripple and its spectrum before and after the LDO; load-step response (a square wave on LOAD); output impedance against frequency (a swept sine on LOAD, LDO~ on an ADC); dropout as TRIM lowers the buck; the buck's pulse-skipping at light load. | LOAD from a DAC (0 to 1 V); TRIM from the other DAC or open; BUCK~ and LDO~ to the two ADCs (the x10 input for the few millivolts of ripple). | Nothing beyond SMA cables. |
| [**c3**](docs/HANDBOOK_amod_c.md#c3) charge pump | A charge pump the FPGA clocks: -5 V from +5 V, whose output resistance is 1 / (f C). | [ICL7660A](https://www.lcsc.com/product-detail/C7881.html), [SN74LV1T34](https://www.ti.com/product/SN74LV1T34) | ICL7660A from the switched 5 V, OSC driven from Pmod IO6 through a 5 V buffer and 1 k (the pump runs at half IO6's frequency); 1 uF flying, 1 uF out, 1 k of load; CAP (the flying capacitor's top, 0-5 V) and OUT (about -5 V) each through 47 k / 10 k, so /5.7. | CAP and OUT are 8.2 k sources: read them at high impedance.  Rout = 1 / (f C) + about 60 ohm: 2 k at 1 kHz on IO6, 80 ohm at 100 kHz.  With no clock on IO6 the pump stops. | Output voltage and ripple against the clock (the 1 / (f C) law); the flying capacitor's charge and dump on CAP; efficiency against load. | A square wave on Pmod IO6 (1 kHz to 100 kHz); OUT and CAP to the ADCs at high impedance. | Gateware on the host (the tutorial's). |
| [**c4**](docs/HANDBOOK_amod_c.md#c4) SC filter | A switched-capacitor filter: a 5th-order Butterworth low-pass whose corner is the FPGA's clock divided by 100. | [MAX7410](https://www.analog.com/en/products/max7410.html), [SN74LV1T34](https://www.ti.com/product/SN74LV1T34) | fc = fCLK / 100, up to 15 kHz (1.5 MHz on IO3, through a 5 V buffer); IN terminated in 49.9 ohm and AC-coupled (1 uF, 100 k: 1.6 Hz); OUT AC-coupled through 1 uF and 49.9 ohm; 5 V from the switch. | IN +-1 V.  There is no anti-alias filter in front: a tone near fCLK folds down into the passband, and the clock's images sit near fCLK at OUT (that is the point).  JLCPCB had 134 MAX7410s on 2026-10-28. | The corner following the clock; aliasing a tone near fCLK; the clock feedthrough on OUT's spectrum; a tracking filter controlled from gateware. | A clock 100 times the corner you want on Pmod IO3; DAC to IN, OUT to an ADC. | Gateware on the host (the tutorial's). |
| [**c5**](docs/HANDBOOK_amod_c.md#c5) SC integrator | A resistor made of a switch and a capacitor, in an integrator: R = 1 / (f C), set by the FPGA's two phases. | [TMUX4053](https://www.ti.com/product/TMUX4053), [OPA810](https://www.ti.com/product/OPA810) | 1 nF switched between IN and ground (phi1, Pmod IO4) and between ground and the summing node (phi2, IO8): the parasitic-insensitive integrator; R = 1 M at 1 kHz, 1 k at 1 MHz.  OPA810 with 10 nF (C0G) and 1 M across it; IN terminated in 49.9 ohm, OUT through 49.9 ohm. | IN +-1 V.  The phases must not overlap (overlap them on purpose to watch IN leak through); the TMUX4053's charge injection shows at high clock rates; the 1 M sets the DC gain (1 M / R). | The 1 / (f C) law measured as the integrator's slope against the clock; a switched-capacitor low-pass (the integrator with the 1 M); overlap and charge injection. | Two non-overlapping square waves on Pmod IO4 and IO8; DAC to IN, OUT to an ADC. | Gateware on the host (the tutorial's). |
| [**c6**](docs/HANDBOOK_amod_c.md#c6) delta-sigma | A second-order delta-sigma modulator with its insides on jacks: a one-bit stream whose density follows IN. | [OPA2810](https://www.ti.com/product/OPA2810), [TLV3501](https://www.ti.com/product/TLV3501), [SN74LVC1G79](https://www.ti.com/product/SN74LVC1G79), [SN74LVC1G3157](https://www.ti.com/product/SN74LVC1G3157) | Two integrators (10 k into 220 pF, 6.8 k into 680 pF) on a 1.65 V virtual ground (the 3.3 V rail halved by 0.1 % resistors); the one-bit DACs switch 10 k between 3.3 V and ground; a TLV3501 and a 74LVC1G79 clocked from Pmod IO1 (about 1 MHz) put the bit on IO7.  Full scale +-1.65 V; INT1 and INT2 through 3.3 k / 1 k (about a quarter, offset 0.38 V). | IN is 10 k (not 50 ohm): drive it from the DAC directly.  Keep IN within +-1.5 V: beyond that the second integrator leaves the comparator's 0-3.3 V input range (10 k protects the comparator; the bits stop meaning anything until IN comes back).  INT1 and INT2 are 770 ohm sources: high impedance.  A DC input near a simple fraction of full scale makes idle tones. | The noise spectrum's 40 dB per decade against AMOD-A's a6 (first order, 20); a sinc3 decimator's bits against the oversampling ratio; idle tones; the integrators' outputs on a scope as the loop runs. | A 1 MHz clock on Pmod IO1; read the bits on IO7 and decimate them; DAC to IN; INT1, INT2 to the ADCs at high impedance. | Gateware on the host (the tutorial's). |
| [**c7**](docs/HANDBOOK_amod_c.md#c7) track and hold | A track-and-hold: OUT follows IN while Pmod IO5 is high and holds when it falls. | [LF398](https://www.ti.com/product/LF398-N) | LF398 on +-5 V, 1 nF C0G hold capacitor; about 4 us to acquire, about 30 mV/s of droop, a few mV of hold step; IN terminated in 49.9 ohm, OUT through 49.9 ohm. | IN +-1 V (on +-5 V the LF398's inputs must stay within +-1.5 V).  The hold step depends on the input level; a sine feeds through while holding. | Acquisition time, droop, pedestal (hold step) against IN, feedthrough, aperture delay against the FPGA's edge; sampling and aliasing with a slow ADC behind it. | A pulse train on Pmod IO5 (high: track); DAC to IN, OUT to an ADC. | Gateware on the host (the tutorial's). |
| [**c8**](docs/HANDBOOK_amod_c.md#c8) comparator | A comparator for a successive-approximation or tracking ADC whose DAC is the host's. | [TLV3201](https://www.ti.com/product/TLV3201) | TLV3201 (40 ns, 1.2 mV of hysteresis) on the 3.3 V rail; IN and DAC each averaged with the rail through matched 0.1 % 10 k, so the comparison is unchanged; BIT on Pmod IO2 (high: IN above DAC). | IN and DAC +-1 V, each 20 k: drive them from 50 ohm sources.  The ADC is as good as the host's DAC: 12 bits needs a 12-bit DAC. | Successive approximation (12 bits in 12 steps), a tracking ADC, single-slope conversion; the host DAC's DNL and INL. | The signal to IN, DAC 2 to DAC; the gateware sets the DAC, reads BIT on IO2 and halves the step. | Gateware on the host (the tutorial's). |
| [**c9**](docs/HANDBOOK_amod_c.md#c9) differential pair | A differential pair on a current mirror: OUT is tanh of the input difference, linear near balance. | [DMMT3904W](https://www.lcsc.com/product-detail/C155305.html), [BCM857BS](https://www.lcsc.com/product-detail/C105896.html), [MMBT3904](https://www.lcsc.com/product-detail/C20526.html), [OPA810](https://www.ti.com/product/OPA810) | A matched NPN pair on a 1 mA tail (an MMBT3904 with -3.4 V on its base), a matched PNP pair as the mirror, an OPA810 transimpedance (1 k) on the output node: OUT = -1 k x (Ic1 - Ic2), +-1 V; gm = Itail / (4 VT), about 10 mS.  IN+ and IN- terminated in 49.9 ohm. | IN+ and IN- +-0.2 V; linear within about +-25 mV of balance; the offset is the pair's VBE match (2 mV). | The tanh transfer and gm; a triangle of +-72 mV into a sine (1.4 % distortion); common-mode rejection (the same signal on both inputs). | DAC 1 to IN+, DAC 2 to IN- (or IN- to a 50 ohm terminator); OUT to an ADC. | Nothing beyond SMA cables. |
| [**c10**](docs/HANDBOOK_amod_c.md#c10) cascode | Common emitter against cascode on one transistor pair: the Miller effect, switched by a jumper. | [DMMT3904W](https://www.lcsc.com/product-detail/C155305.html), [MMBT3904](https://www.lcsc.com/product-detail/C20526.html) | Q1 at about 1.4 mA, 100 ohm in its emitter, 1 k collector load; Q2 its cascode (base at 2.4 V); Q3 an emitter follower into 1 uF and 51 ohm; IN terminated, AC-coupled and through 2.2 k.  Gain about -8 at Q1's collector, -6 from IN, -3 into 50 ohm. | IN +-50 mV.  The jumper on the header shorts the cascode (common emitter, about 2 MHz wide); parked on one pin it leaves the cascode in (several times wider). | Bandwidth with and without the cascode; the Miller capacitance computed from the corner and the 2.2 k; gain against the emitter resistor. | DAC to IN, OUT to an ADC; sweep the frequency once with the jumper on and once parked. | Nothing beyond SMA cables. |
| [**c11**](docs/HANDBOOK_amod_c.md#c11) 555 | A 555 as a voltage-controlled oscillator: CV moves its thresholds and so its frequency. | [TLC555](https://www.ti.com/product/TLC555) | TLC555 astable from the switched 5 V, 1 k and 10 k with 10 nF C0G: about 6.9 kHz; CV terminated and through 2.2 k into the control pin; OUT through 3.9 k / 1 k (about 1 V). | CV +-1 V; OUT is a 800 ohm source, read it at high impedance.  The frequency falls as CV rises. | Frequency against CV; the capacitor's ramp between 1/3 and 2/3 of the supply; a voltage-to-frequency ADC counted in the FPGA. | CV from a DAC; OUT to an ADC. | Nothing beyond SMA cables. |
| [**c12**](docs/HANDBOOK_amod_c.md#c12) rectifier | A precision full-wave rectifier: OUT = \|IN\|, with no diode drop. | [OPA2197](https://www.ti.com/product/OPA2197), [BAT54S](https://www.lcsc.com/product-detail/C8592.html) | An OPA2197 inverts IN through two Schottky diodes so its node X is -IN for positive inputs and 0 for negative ones; the second half sums -(IN + 2 X); IN terminated in 49.9 ohm, OUT through 49.9 ohm. | IN +-1 V; DC to about 100 kHz, above which the first stage's slew across the diodes leaves a glitch at each zero crossing. | Rectifying with no dead zone; the glitch against frequency; an AC voltmeter (rectify and average); AM detection. | DAC to IN, OUT to an ADC. | Nothing beyond SMA cables. |

More on each tile, with its picture, in the [AMOD-C handbook](docs/HANDBOOK_amod_c.md); what to buy in [KIT.md](docs/KIT.md).

<!-- /board:amod_c -->

<!-- board:amod_m -->
### [AMOD-M](docs/HANDBOOK_amod_m.md): the motor board

| tile | what it does | chip | specs | limits | experiments | how to use it | you need |
|---|---|---|---|---|---|---|---|
| [**m1**](docs/HANDBOOK_amod_m.md#m1) power | Power: 5 V from USB-C, and -5 V and 3.3 V made from it; a socket carries the rails to a breadboard (AMOD-A's a1). | [LM2664](https://www.ti.com/product/LM2664), [TPS7A20](https://www.ti.com/product/TPS7A20) | +5 V up to 1.5 A, -5 V at 40 mA, +3.3 V at 300 mA; green LED 5 V, red LED -5 V. | -5 V is 40 mA: the op amps on +-5 V (m3, m7, m9, m10, m11) draw about 15 mA together.  The board negotiates nothing: use a plain 5 V supply. | - | Plug in the USB-C (and the host's Pmod (rev A boards: ECP5-2ADC-2DAC rev A only, its sockets are non-standard as this plug is) for m3 and m4); then switch on each tile you use (slider up). | A 5 V USB-C supply, 1.5 A or more (kit: Raspberry Pi 5.1 V 3 A supply). |
| [**m2**](docs/HANDBOOK_amod_m.md#m2) motor supply | The motor supply VMOT: a barrel jack (5-16 V) or USB's 5 V, each through a Schottky; its voltage / 16 on a jack. | [SS34](https://www.lcsc.com/product-detail/C8678.html), [SMBJ16A](https://www.lcsc.com/product-detail/C353386.html) | DC-005 5.5 / 2.1 mm jack, centre positive; two SS34 (3 A) into VMOT, so VMOT is the larger input less about 0.4 V; SMBJ16A (clamps near 26 V) and 220 uF on VMOT soak up a motor's braking energy (the diodes stop it reaching the supply); green LED; VM = VMOT / 16 (15 k / 1 k) through 49.9 ohm. | 5-16 V in.  VMOT is not switched and has no fuse: the supply's current limit is the board's.  With USB alone VMOT is about 4.6 V, enough for the small motors (the DRV8251A's lockout is 4.45 V at most).  VM is a 1 k source: read it at high impedance. | The supply's droop and the braking energy coming back onto VMOT (VM on an ADC while m3 brakes). | The supply on the barrel jack: 12 V for the stepper and the solenoid, about 6 V for the N20 and m7's 8 ohm speaker; VM to an ADC to watch VMOT. | From the kit (docs/KIT.md, Motors and actuators): a 3-12 V adjustable supply with a barrel plug (PhMOD's h4 and AMOD-B's b2 take the same one). |
| [**m3**](docs/HANDBOOK_amod_m.md#m3) DC motor | A brushed DC motor with its encoder: drive, brake or coast from two FPGA lines; its current and its terminal voltage on jacks. | [DRV8251A](https://www.ti.com/product/DRV8251A), [OPA2171](https://www.ti.com/product/OPA2171), [TPS7A20](https://www.ti.com/product/TPS7A20) | DRV8251A (4.1 A H-bridge) from VMOT: IN1 on Pmod IO7, IN2 on IO1 (both low: coast, then sleep after 1 ms).  Current limit 2 A (VREF 2.0 V from the switched 5 V, 620 ohm on IPROPI); I = the motor's current, 0.98 V/A, buffered by an OPA2171 through 49.9 ohm; V = (M1 - M2) / 13 through 49.9 ohm.  JST PH 6-way: 1 M1, 2 GND, 3 encoder A (IO5), 4 encoder B (IO6), 5 3.3 V (its own TPS7A2033), 6 M2. | 2 A (cycle by cycle above it); IPROPI reads only while a low-side FET conducts (drive and brake, not coast).  V's +-1 V range covers +-13 V at the motor.  The encoder needs its own pull-ups or the FPGA's.  Encoder motors' pin orders differ: check yours against the PH's. | Speed against duty cycle; drive / brake against drive / coast; the back-EMF in the coast intervals as a speed sensor with no encoder; the motor constant (Kt = Ke) from V and the encoder's speed; speed and position loops in gateware; current limiting under stall. | PWM on IO7 (forward) or IO1 (reverse); the encoder into the gateware from IO5 and IO6; I and V to the ADCs. | From the kit (docs/KIT.md, Motors and actuators): an N20 or 25 mm gearmotor with a hall encoder on a JST PH 6-way lead. |
| [**m4**](docs/HANDBOOK_amod_m.md#m4) stepper | A bipolar stepper: two DRV8251A from four FPGA lines; each coil's current on a jack. | [DRV8251A](https://www.ti.com/product/DRV8251A) | Coil A IN1 on Pmod IO2, IN2 on IO3; coil B IN1 on IO4, IN2 on IO8 (each pulled down: both low is coast).  VREF 1.0 V: 1 A per coil, and the tile's switch takes the limit to zero; IA, IB = each coil's current through 10 k (0.98 V/A, read at high impedance).  JST XH 4-way: 1 A+, 2 A-, 3 B+, 4 B- (each driver's OUT2 on its coil's + pin: a stepper does not notice). | 1 A per coil.  IA and IB read the current's size, not its sign, and only while a low side conducts. | Full, half and PWM microstepping in gateware; resonance and missed steps against the step rate; the coil current's rise against the supply voltage (L / R); stall detection from the current. | The step sequence on IO2, IO3, IO4, IO8; IA and IB to the ADCs at high impedance. | From the kit (docs/KIT.md, Motors and actuators): a NEMA 17 class bipolar stepper under 1 A per phase, with a JST XH 4-way lead. |
| [**m5**](docs/HANDBOOK_amod_m.md#m5) servo | A hobby servo: a DAC's pulse squared to 5 V for the servo, and the servo's supply current on a jack. | [TLV3501](https://www.ti.com/product/TLV3501), [INA181](https://www.ti.com/product/INA181) | CMD (0 / +1 V, terminated in 49.9 ohm) through 10 k into a TLV3501 (threshold 0.49 V) on the switched 5 V; 3-pin header S, +5 V, GND (top to bottom); the servo's ground returns through 0.05 ohm, read by an INA181A1 (x20): I = 1 V/A through 49.9 ohm. | The servo runs from the switched 5 V (USB's): a micro servo's stall current (about 0.7 A) is fine, a big servo's is not.  I reads one way only. | Angle against pulse width (1-2 ms every 20 ms); the servo's current while it slews and when it is held against a load; its internal loop's step response. | A 1-2 ms pulse every 20 ms from a DAC on CMD; I to an ADC. | From the kit (docs/KIT.md, Motors and actuators): an SG90 or MG90S micro servo. |
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
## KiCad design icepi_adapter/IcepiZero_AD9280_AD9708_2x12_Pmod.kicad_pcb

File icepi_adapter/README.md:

# The Icepi Zero adapter with a Pmod (the fourth board)

The tutorial's 2x12 adapter (`~/mudd/133electronics/icepi-zero-dac-adc/adapter_board/`) with a 2 x 6 right-angle Pmod
socket on a 15 mm extension of its right-hand end, so an Icepi Zero can drive a Pmod board while the AD9280/AD9708 module
sits on top as before.  Never built.

- **Its socket follows the Pmod specification (since 2026-11-16).**  J3 is the spec's figure 5, a host socket on an east
  edge: pin 1 at the north end (toward the Icepi header), IO1-4 on the row far from the opening, 3.3 V and ground at the
  south end.  A Digilent module, or any module drawn to the spec, plugs in component side up.  Until 2026-11-16 the
  socket was mirrored end to end, as ECP5-2ADC-2DAC rev A's J303/J304 are; the old files are in this folder's git history.
- **The AMOD and RF-MOD rev A plugs are not standard** (`../bringup/REVB.md` 1.15): one fits this socket **only upside
  down**, with `pmod[0..3]` and `pmod[4..7]` swapped in the `.lpf`.  The right way up it puts its 3.3 V on IO1 and IO5
  and its ground on IO2 and IO6: never plug one in that way.  Rev B's plugs follow the spec and fit the right way up.
- **Source of truth:** `~/OpticsPCBs/IcepiZeroADCDAC/adapters/make_boards.py`, board `adda12p` (`PMOD_LAYOUT = "spec"`).
  These files are copies of its `out/IcepiZero_AD9280_AD9708_2x12_Pmod/`, taken 2026-11-16 at 15:03 from that
  repository's working tree (uncommitted there at the time, on top of 677b57e); rebuild there with
  `KICAD=10 ../kicad-python.sh make_boards.py adda12p` and copy back.  Its README section "The 2x12 with a Pmod" has the
  reasons, and `~/OpticsPCBs/tools/pin_audit/connectors/IcepiZero_pmod_adapter.py` checks J3 against the spec by position.
- **80 x 30 mm, four layers.**  Checked here on the copy: KiCad 10.0.7's DRC finds 0 violations, 0 unconnected pads and
  0 schematic-parity issues, and every J3 pad's net is the spec's for its pin (Pmod pin k on pad 13-2k, pin k+6 on pad
  14-2k: IO1-4 on pads 11, 9, 7, 5; IO5-8 on 12, 10, 8, 6; ground on 3 and 4; 3.3 V on 1 and 2).  The eight Pmod lines
  run on In2 between the through-hole pads, In1 is solid ground, the outer layers keep the original fan-out.
- **Pins** (`*-pinmap.csv`, `*.lpf`): the `.lpf` names them `pmod[0]` ... `pmod[7]` for IO1-8 as before, **but the balls
  behind the names moved** with the redraw (`pmod[0]` was N1, now F2):

| Pmod | pin | Icepi header pin | GPIO | ECP5 ball |
|---|---|---|---|---|
| IO1 | 1 | 40 | 21 | F2 |
| IO2 | 2 | 36 | 16 | H3 |
| IO3 | 3 | 27 | 0 | G3 |
| IO4 | 4 | 10 | 15 | N1 |
| IO5 | 7 | 38 | 20 | F1 |
| IO6 | 8 | 28 | 1 | K3 |
| IO7 | 9 | 22 | 25 | J2 |
| IO8 | 10 | 8 | 14 | P1 |
| GND | 5, 11 | | | |
| 3.3 V | 6, 12 | 1 | | |

Header pins 3 and 5 (GPIO2, GPIO3; T2, R2) are spare.

- **Order:** upload `IcepiZero_AD9280_AD9708_2x12_Pmod-gerbers.zip` at JLCPCB as a 4-layer, 1.6 mm board (the price was not
  checked on the day).  Hand-solder J1 (2 x 20 female, 2.54 mm, on the BOTTOM: it takes the Icepi Zero's header), J2 (2 x 12 male, top,
  for the module) and J3 (2 x 6 right-angle female, 2.54 mm, e.g. HC-PM254-8.5H-2x6PW, LCSC C22373932; housing face at
  the board edge).  Nothing else changes from the 2x12 adapter's instructions.
- **Heights.**  The adapter's board sits about 11 mm above the Icepi Zero's (the header's 2.5 mm of plastic plus J1's
  8.5 mm), and a Pmod board's plug mates only with its own board level with the adapter's: raise the board on a
  spacer under its feet, or use a 2 x 6 Pmod extension cable (the easier way, and the ECP5 board needs none).

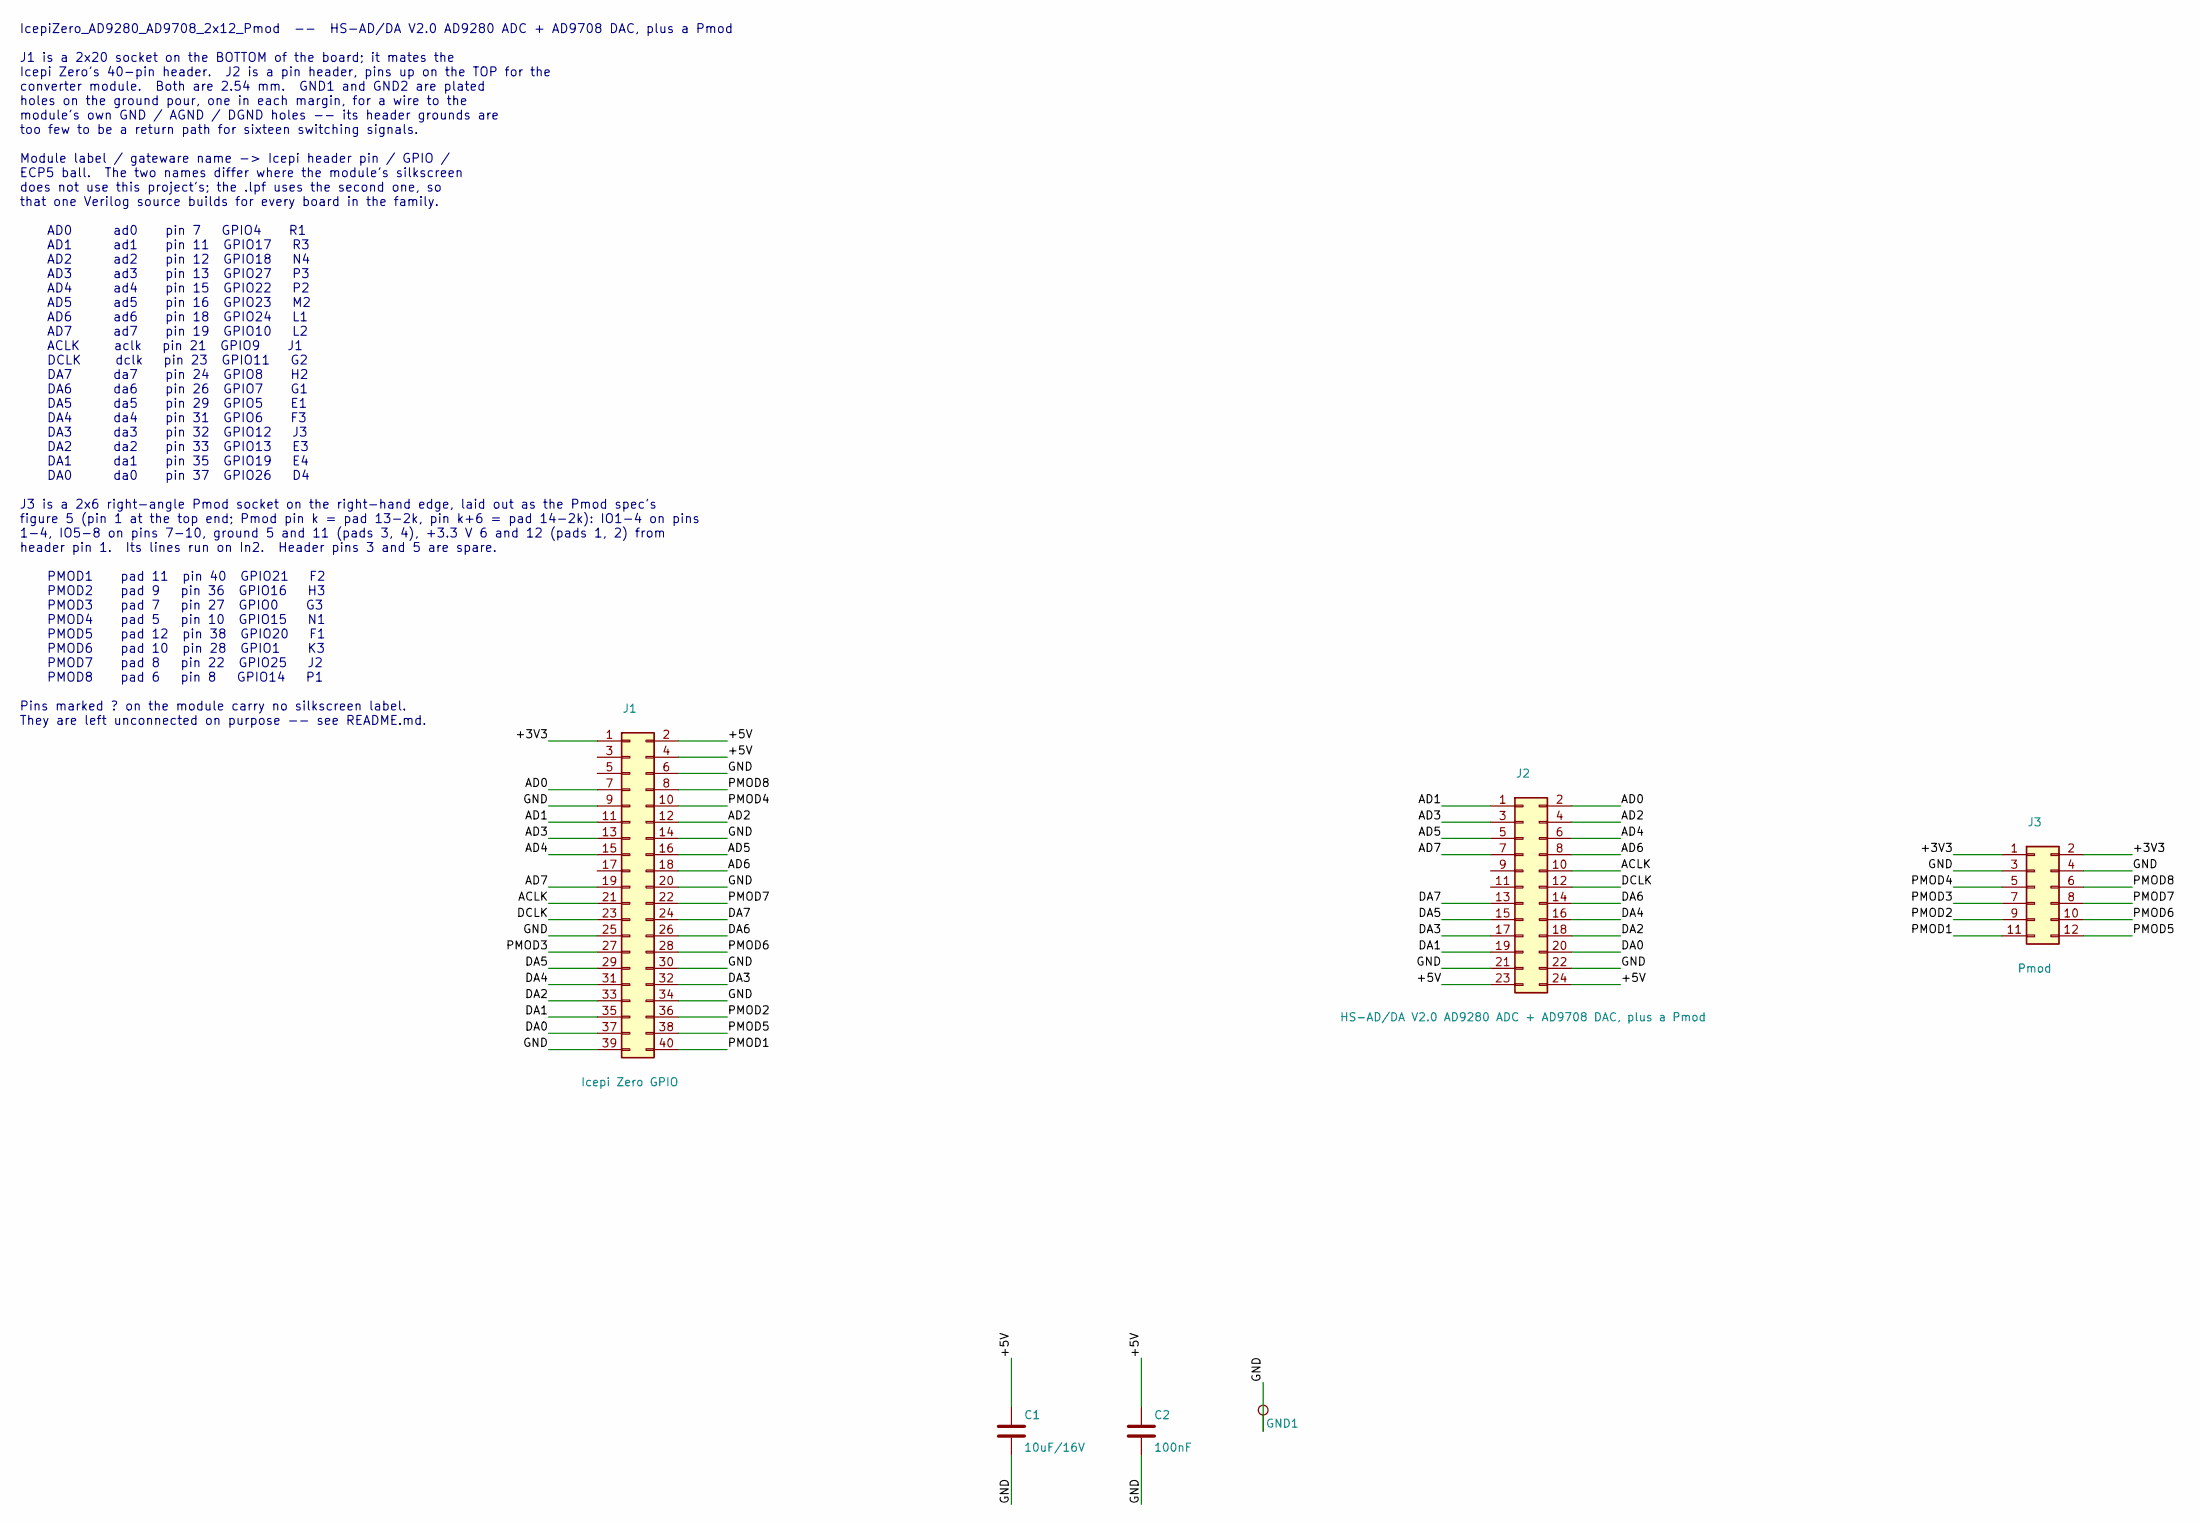
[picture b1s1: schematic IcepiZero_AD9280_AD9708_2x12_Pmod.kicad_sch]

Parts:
C1: 10uF/16V; C_0805_2012Metric
C2: 100nF; C_0603_1608Metric
GND1: GND; TestPoint_THTPad_1.5x1.5mm_Drill0.7mm
J1: Icepi Zero GPIO; PinSocket_2x20_P2.54mm_Vertical
J2: HS-AD/DA V2.0 AD9280 ADC + AD9708 DAC, plus a Pmod; PinHeader_2x12_P2.54mm_Vertical
J3: Pmod; PinSocket_2x06_P2.54mm_Horizontal

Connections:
+3V3: J1.1, J3.1, J3.2
+5V: C1.1, C2.1, J1.2, J1.4, J2.23, J2.24
ACLK: J1.21, J2.10
AD0: J1.7, J2.2
AD1: J1.11, J2.1
AD2: J1.12, J2.4
AD3: J1.13, J2.3
AD4: J1.15, J2.6
AD5: J1.16, J2.5
AD6: J1.18, J2.8
AD7: J1.19, J2.7
DA0: J1.37, J2.20
DA1: J1.35, J2.19
DA2: J1.33, J2.18
DA3: J1.32, J2.17
DA4: J1.31, J2.16
DA5: J1.29, J2.15
DA6: J1.26, J2.14
DA7: J1.24, J2.13
DCLK: J1.23, J2.12
GND: C1.2, C2.2, GND1.1, J1.6, J1.9, J1.14, J1.20, J1.25, J1.30, J1.34, J1.39, J2.21, J2.22, J3.3, J3.4
PMOD1: J1.40, J3.11
PMOD2: J1.36, J3.9
PMOD3: J1.27, J3.7
PMOD4: J1.10, J3.5
PMOD5: J1.38, J3.12
PMOD6: J1.28, J3.10
PMOD7: J1.22, J3.8
PMOD8: J1.8, J3.6

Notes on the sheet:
IcepiZero_AD9280_AD9708_2x12_Pmod -- HS-AD/DA V2.0 AD9280 ADC + AD9708 DAC, plus a Pmod J1 is a 2x20 socket on the BOTTOM of the board; it mates the Icepi Zero's 40-pin header. J2 is a pin header, pins up on the TOP for the converter module. Both are 2.54 mm. GND1 and GND2 are plated holes on the g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

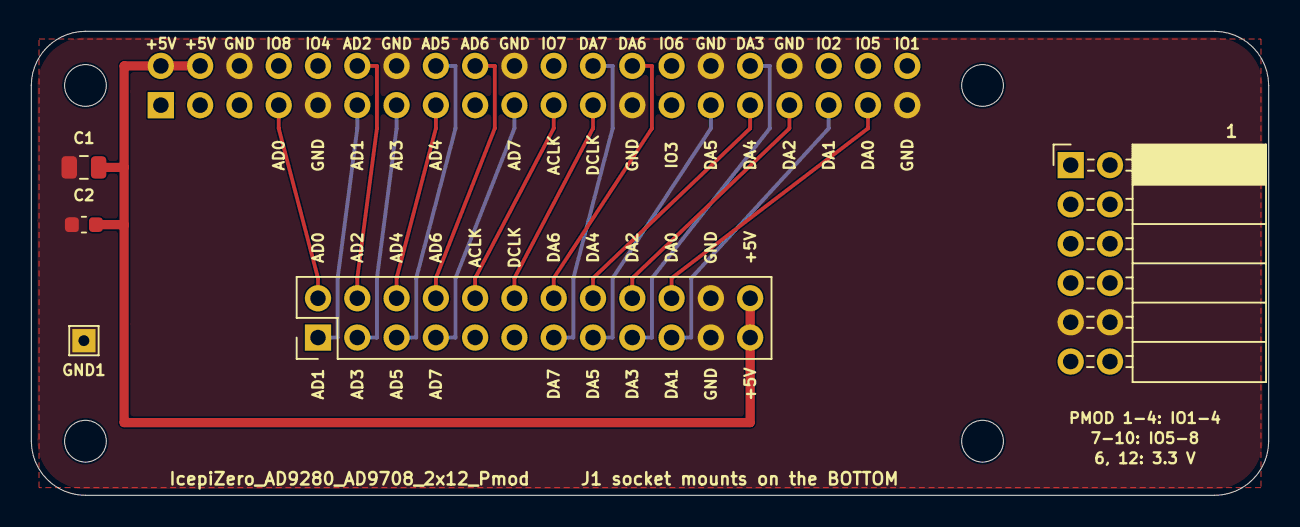
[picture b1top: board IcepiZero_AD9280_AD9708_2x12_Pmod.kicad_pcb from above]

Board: 4 copper layers, 80.0 x 30.0 mm, 10 parts (1 on the bottom side), 29 nets.

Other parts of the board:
H1, H2, H3, H4: M2.5; MountingHole_2.7mm_M2.5_ISO7380

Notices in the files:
README.md:
License:
Open hardware and open source: `LICENSE` says which licence covers what (the hardware is CERN-OHL-P-2.0,
`LICENSE-HARDWARE.txt`).
hardware/amod_a.kicad_sch:
Board: Jason Gallicchio and Claude  |  open hardware, CERN-OHL-P-2.0  |  github.com/gallicchio/AMOD-and-RFMOD
